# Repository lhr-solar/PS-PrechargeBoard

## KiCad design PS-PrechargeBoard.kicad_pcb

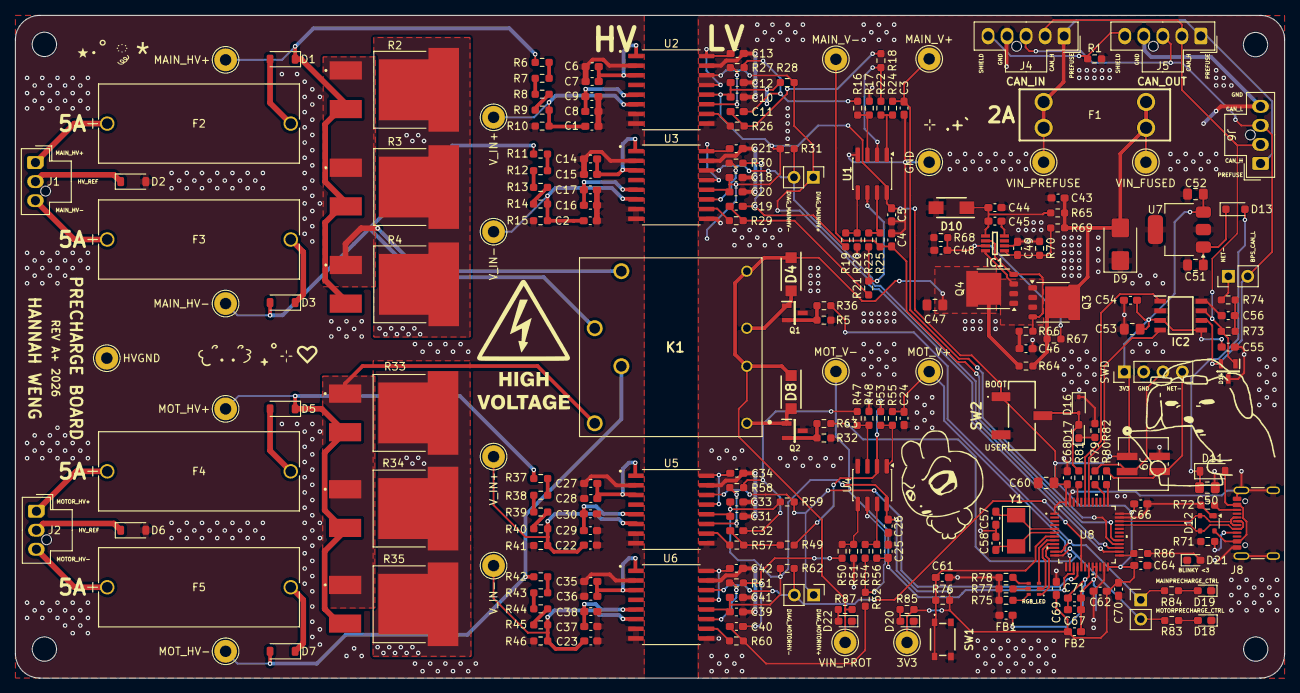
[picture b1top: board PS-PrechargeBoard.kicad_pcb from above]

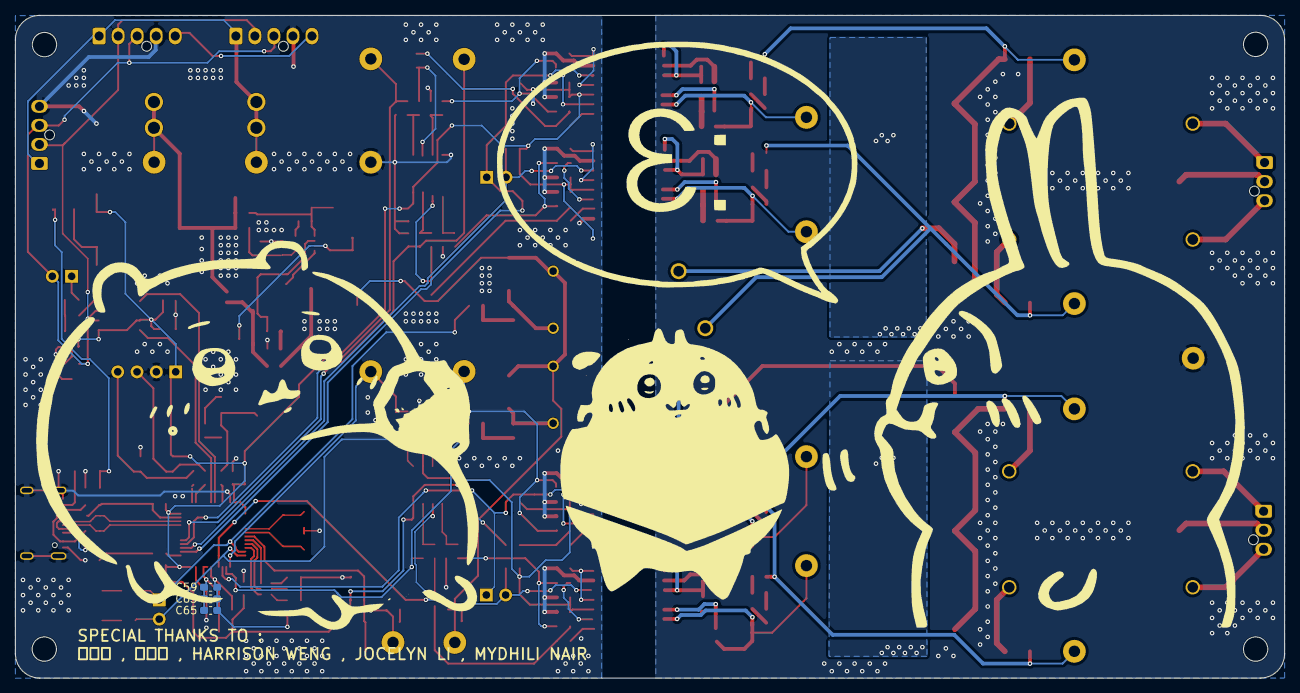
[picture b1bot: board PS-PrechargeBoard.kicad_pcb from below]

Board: 2 copper layers, 166.9 x 87.1 mm, 239 parts (3 on the bottom side), 139 nets.

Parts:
C1, C2, C5, C10, C18, C22, C23, C26, C31, C39, C44, C65, C67: 1u; C_0603_1608Metric_Pad1.08x0.95mm_HandSolder
C3, C4, C11, C19, C24, C25, C32, C40, C46: 10n; C_0603_1608Metric_Pad1.08x0.95mm_HandSolder
C6, C9, C12, C14, C17, C20, C27, C30, C33, C35, C38, C41: 1n; C_0603_1608Metric_Pad1.08x0.95mm_HandSolder
C7, C8, C13, C15, C16, C21, C28, C29, C34, C36, C37, C42, C71: 100n; C_0603_1608Metric_Pad1.08x0.95mm_HandSolder
C43, C48, C49, C54, C55, C56, C59, C61, C62, C63, C64, C66, C68, C69, C70: 0.1u; C_0603_1608Metric_Pad1.08x0.95mm_HandSolder
C45: 220n; C_0603_1608Metric_Pad1.08x0.95mm_HandSolder
C47, C50, C51, C52, C53, C60: 10u; C_0805_2012Metric_Pad1.18x1.45mm_HandSolder
C57, C58: 26p; C_0603_1608Metric_Pad1.08x0.95mm_HandSolder
D1, D2, D3, D5, D6, D7: RSX068MP2STR; D_SOD-123
D4, D8: VSSAF510HM3/H; SODFL5226X100N
D9: SMBJ15CA; D_SMB
D10: SMAF4758A; SODFL5026X125N
D11: D_Schottky; D_SOD-123
D12: SP0503BAHT; SOT-143
D13: SBA130CH-AU_R1_000A1; D_SOD-323_HandSoldering
D14: CDSOT23-T24CAN
D15: RGB_LED
D16: TVS; D_SOD-323
D17, D18, D19, D20, D21, D22: LED; LED_0603_1608Metric_Pad1.05x0.95mm_HandSolder
F1: 2A; Fuse-3557-2
F2, F3, F4, F5: 5A; HV-Fuse
FB1, FB2: FerriteBead; C_0603_1608Metric_Pad1.08x0.95mm_HandSolder
H1, H2, H3, H4: MountingHole; MountingHole_3.2mm_M3
IC1: LM74502DDFR
IC2: TCAN3413DR
J1: HV_Main; Molex_Nano-Fit_105309-xx03_1x03_P2.50mm_Vertical
J2: HV_Motor; Molex_Nano-Fit_105309-xx03_1x03_P2.50mm_Vertical
J3: MOTOR_DIAG; PinHeader_1x02_P2.54mm_Vertical
J4: CAN_IN; Molex_Nano-Fit_105309-xx05_1x05_P2.50mm_Vertical
J5: CAN_OUT; Molex_Nano-Fit_105309-xx05_1x05_P2.50mm_Vertical
J6: DEBUG_NANO; Molex_Nano-Fit_105309-xx04_1x04_P2.50mm_Vertical
J7: PRECHARGE_CTRL; PinHeader_1x02_P2.54mm_Vertical
J8: USB_C_Receptacle_USB2.0_16P; USB_C_Receptacle_GCT_USB4105-xx-A_16P_TopMnt_Horizontal
J9: SWD_Header; SWD_Conn
J10: SWD; PinHeader_1x04_P2.54mm_Vertical
J11: MAIN_DIAG; PinHeader_1x02_P2.54mm_Vertical
JP1: TRM; PinHeader_1x02_P2.54mm_Vertical
K1: FTR-J2AK012W; FTRJ2AK012W
Q1, Q2: NMOS; SOT95P237X112-3N
Q3, Q4: PSMN012-100YS; LFPAK56
R1, R64: 0; R_0603_1608Metric_Pad0.98x0.95mm_HandSolder
R2, R3, R4, R33, R34, R35: 50; RES_PWR263S-35-3300F
R5, R10, R15, R16, R17, R18, R19, R20, R21, R22, R23, R32, R41, R46, R47, R48, R49, R50, R51, R52, R53, R54, R65, R76, R81: 10k; R_0603_1608Metric_Pad0.98x0.95mm_HandSolder
R6, R7, R8, R9, R11, R12, R13, R14, R37, R38, R39, R40, R42, R43, R44, R45: 180k; R_0603_1608Metric_Pad0.98x0.95mm_HandSolder
R24, R25, R26, R27, R29, R30, R55, R56, R57, R58, R60, R61: 10; R_0603_1608Metric_Pad0.98x0.95mm_HandSolder
R28, R31, R59, R62: 47k; R_0603_1608Metric_Pad0.98x0.95mm_HandSolder
R36, R63: 100; R_0603_1608Metric_Pad0.98x0.95mm_HandSolder
R66: 33; R_0603_1608Metric_Pad0.98x0.95mm_HandSolder
R67, R69: 100k; R_0603_1608Metric_Pad0.98x0.95mm_HandSolder
R68: 7.32k; R_0603_1608Metric_Pad0.98x0.95mm_HandSolder
R70: 15.8k; R_0603_1608Metric_Pad0.98x0.95mm_HandSolder
R71, R72: 5.1k; R_0603_1608Metric_Pad0.98x0.95mm_HandSolder
R73, R74: 60; R_0603_1608Metric_Pad0.98x0.95mm_HandSolder
R75, R77, R78, R82, R83, R84, R85, R86: 1k; R_0603_1608Metric_Pad0.98x0.95mm_HandSolder
R79, R80: 22; R_0603_1608Metric_Pad0.98x0.95mm_HandSolder
R87: 4.7k; R_0603_1608Metric_Pad0.98x0.95mm_HandSolder
SW1: Reset; TL3365AF180QG
SW2: SW_SPDT; BootSW
TP1: MOT_HV+; TestPoint_THTPad_D3.0mm_Drill1.5mm
TP2: MAIN_HV+; TestPoint_THTPad_D3.0mm_Drill1.5mm
TP3: HVGND; TestPoint_THTPad_D3.0mm_Drill1.5mm
TP4: MAIN_HV-; TestPoint_THTPad_D3.0mm_Drill1.5mm
TP5: MOT_HV-; TestPoint_THTPad_D3.0mm_Drill1.5mm
TP6: 3V3; TestPoint_THTPad_D3.0mm_Drill1.5mm
TP7: VIN_PROT; TestPoint_THTPad_D3.0mm_Drill1.5mm
TP8: VIN_PREFUSE; TestPoint_THTPad_D3.0mm_Drill1.5mm
TP9: MAIN_V+; TestPoint_THTPad_D3.0mm_Drill1.5mm
TP10: MAIN_V-; TestPoint_THTPad_D3.0mm_Drill1.5mm
TP11: GND; TestPoint_THTPad_D3.0mm_Drill1.5mm
TP12: VIN_FUSED; TestPoint_THTPad_D3.0mm_Drill1.5mm
TP13: MOT_V+; TestPoint_THTPad_D3.0mm_Drill1.5mm
TP14: MOT_V-; TestPoint_THTPad_D3.0mm_Drill1.5mm
TP15, TP19: V_IN+; TestPoint_THTPad_D3.0mm_Drill1.5mm
TP16, TP20: V_IN-; TestPoint_THTPad_D3.0mm_Drill1.5mm
U1, U4: TLV9002QDRQ1; SOIC-8_3.9x4.9mm_P1.27mm
U2, U3, U5, U6: SOIC127P1030X265-16N
U7: MCP1826S; SOT-223-3_TabPin2
U8: STM32G473CETx; 48PinMCU
Y1: Crystal; Crystal_SMD_Abracon_ABM3-2Pin_5.0x3.2mm

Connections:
3V3: C5.1, C10.1, C12.1, C18.1, C20.1, C26.1, C31.1, C33.1, C39.1, C41.1, C52.2, C53.1, C54.1, C55.1, C60.1, C62.1, C64.1, C66.1, C68.1, C69.1, C70.1, FB2.1, IC2.3 (VCC), IC2.5 (SHDNV_IO), J9.1, J10.1, R28.1, R31.1, R59.1, R62.1, R76.2, R85.1, SW2.1 (A), TP6.1 (1_1), U1.8 (V+), U2.12 (VDD), U3.12 (VDD), U4.8 (V+), U5.12 (VDD), U6.12 (VDD), U7.3 (VO), U8.1 (VBAT), U8.24 (VDD), U8.36 (VDD), U8.48 (VDD)
/48PinMCU/BOOT0: R81.1, U8.45 (PB8-BOOT0)
/48PinMCU/GNDA: C59.2, C63.2, C65.2, C67.2, C71.2, FB1.1, U8.19 (VSSA)
/48PinMCU/NRST: C61.1, R76.1, SW1.1, U8.7 (PG10-NRST)
/48PinMCU/PA0: D15.5, U8.8 (PA0-GPIO_BLUE)
/48PinMCU/PA1: D15.3, U8.9 (PA1_GPIO_RED)
/48PinMCU/PA2: D15.1, U8.10 (PA2-GPIO_GREEN)
/48PinMCU/SWCLK: R79.1, U8.38 (PA14)
/48PinMCU/SWDIO: R80.1, U8.37 (PA13)
/48PinMCU/VDDA: C59.1, C63.1, C65.1, C67.1, C71.1, FB2.2, U8.20 (VREF+), U8.21 (VDDA)
/BLINKY: R86.1, U8.25 (PB11)
/BPS_CAN_H: D14.1 (CAN_H), IC2.7 (CANH), J4.2 (CAN_H), J5.2 (CAN_H), J6.2 (CAN_H), R73.1
/BPS_CAN_L: D14.2 (CAN_L), IC2.6 (CANL), J4.3 (CAN_L), J5.3 (CAN_L), J6.3 (CAN_L), JP1.2 (B)
/CAN_RX: IC2.4 (RXD), U8.42 (PB5)
/CAN_TX: IC2.1 (TXD), U8.43 (PB6)
/DIAG_MAINHV+: J11.1, R28.2, U2.14 (DIAG), U8.26 (PB12)
/DIAG_MAINHV-: J11.2, R31.2, U3.14 (DIAG), U8.27 (PB13)
/DIAG_MOTORHV+: J3.1, R59.2, U5.14 (DIAG), U8.16 (PB0)
/DIAG_MOTORHV-: J3.2, R62.2, U6.14 (DIAG), U8.17 (PB1)
/LV Power/PowerProtection/EN/UVLO: C49.1, IC1.1 (EN/UVLO), R69.2, R70.2
/LV Power/PowerProtection/OV: C48.1, IC1.7 (OV), R67.2, R68.1
/LV Power/PowerProtection/gate: IC1.6 (GATE), Q3.4, Q4.4, R66.2
/LV Power/PowerProtection/source: IC1.8 (SRC), Q3.1, Q3.2, Q3.3, Q4.1, Q4.2, Q4.3
/LV Power/USB-C_Connector/CC1: J8.A5 (CC1), R71.2
/LV Power/USB-C_Connector/CC2: J8.B5 (CC2), R72.2
/LV Power/USB-C_Connector/VBUS_IN: D11.2 (A), D12.4 (K), J8.A4 (VBUS), J8.A9 (VBUS), J8.B4 (VBUS), J8.B9 (VBUS)
/LV Power/USB_5V: C50.2, D11.1 (K), D13.2 (A)
/MAINPRECHARGE_CTRL: J7.1, R36.1, R84.1, U8.11 (PA3)
/MAIN_RES_HV-: K1.8 (COM_2), R2.1, R3.1, R4.1
/MAIN_V+: C3.1, R24.2, TP9.1 (1_1), U8.28 (PB14)
/MAIN_V-: C4.1, R25.2, TP10.1 (1_1), U8.29 (PB15)
/MOTPRECHARGE_CTRL: J7.2, R63.1, R83.1, U8.12 (PA4)
/MOT_RES_HV-: K1.5 (NO_1), R33.1, R34.1, R35.1
/MOT_V+: C24.1, R55.2, TP13.1 (1_1), U8.14 (PA6)
/MOT_V-: C25.1, R56.2, TP14.1 (1_1), U8.15 (PA7)
/Main_Fuse/HV_PREFUSE+: F2.1, J1.1
/Main_Fuse/HV_PREFUSE-: F3.1, J1.3
/Main_Fuse/HV_REF: D2.1 (K), J1.2
/Main_Fuse/RESISTOR: R2.3, R3.3, R4.3
/Main_VoltageSensor/OUTN_HV+: C11.1, R18.1, R26.2
/Main_VoltageSensor/OUTN_HV-: C19.1, R21.1, R29.2
/Main_VoltageSensor/OUTP_HV+: C11.2, R16.1, R27.2
/Main_VoltageSensor/OUTP_HV-: C19.2, R19.1, R30.2
/Main_VoltageSensor/V_IN+: C1.1, R9.2, R10.1, TP15.1 (1_1), U2.6 (IN)
/Main_VoltageSensor/V_IN-: C2.1, R14.2, R15.1, TP16.1 (1_1), U3.6 (IN)
/Main_VoltageSensor/VoltageSensor_HV+/3V3_DCDC: C13.2, U2.13 (LDO_OUT), U2.16 (DCDC_IN)
/Main_VoltageSensor/VoltageSensor_HV+/HLDO_OUT: C8.2, C9.2, U2.5 (HLDO_OUT)
/Main_VoltageSensor/VoltageSensor_HV+/HV_DCDC: C6.1, C7.2, U2.1 (DCDC_OUT), U2.3 (HLDO_IN)
/Main_VoltageSensor/VoltageSensor_HV+/OUTN: R26.1, U2.10 (OUTN)
/Main_VoltageSensor/VoltageSensor_HV+/OUTP: R27.1, U2.11 (OUTP)
/Main_VoltageSensor/VoltageSensor_HV-/3V3_DCDC: C21.2, U3.13 (LDO_OUT), U3.16 (DCDC_IN)
/Main_VoltageSensor/VoltageSensor_HV-/HLDO_OUT: C16.2, C17.2, U3.5 (HLDO_OUT)
/Main_VoltageSensor/VoltageSensor_HV-/HV_DCDC: C14.1, C15.2, U3.1 (DCDC_OUT), U3.3 (HLDO_IN)
/Main_VoltageSensor/VoltageSensor_HV-/OUTN: R29.1, U3.10 (OUTN)
/Main_VoltageSensor/VoltageSensor_HV-/OUTP: R30.1, U3.11 (OUTP)
/Motor_Fuse/HV_PREFUSE+: F4.1, J2.1
/Motor_Fuse/HV_PREFUSE-: F5.1, J2.3
/Motor_Fuse/HV_REF: D6.1 (K), J2.2
/Motor_Fuse/RESISTOR: R33.3, R34.3, R35.3
/Motor_VoltageSensor/OUTN_HV+: C32.1, R49.1, R57.2
/Motor_VoltageSensor/OUTN_HV-: C40.1, R52.1, R60.2
/Motor_VoltageSensor/OUTP_HV+: C32.2, R47.1, R58.2
/Motor_VoltageSensor/OUTP_HV-: C40.2, R50.1, R61.2
/Motor_VoltageSensor/V_IN+: C22.1, R40.2, R41.1, TP19.1 (1_1), U5.6 (IN)
/Motor_VoltageSensor/V_IN-: C23.1, R45.2, R46.1, TP20.1 (1_1), U6.6 (IN)
/Motor_VoltageSensor/VoltageSensor_HV+/3V3_DCDC: C34.2, U5.13 (LDO_OUT), U5.16 (DCDC_IN)
/Motor_VoltageSensor/VoltageSensor_HV+/HLDO_OUT: C29.2, C30.2, U5.5 (HLDO_OUT)
/Motor_VoltageSensor/VoltageSensor_HV+/HV_DCDC: C27.1, C28.2, U5.1 (DCDC_OUT), U5.3 (HLDO_IN)
/Motor_VoltageSensor/VoltageSensor_HV+/OUTN: R57.1, U5.10 (OUTN)
/Motor_VoltageSensor/VoltageSensor_HV+/OUTP: R58.1, U5.11 (OUTP)
/Motor_VoltageSensor/VoltageSensor_HV-/3V3_DCDC: C42.2, U6.13 (LDO_OUT), U6.16 (DCDC_IN)
/Motor_VoltageSensor/VoltageSensor_HV-/HLDO_OUT: C37.2, C38.2, U6.5 (HLDO_OUT)
/Motor_VoltageSensor/VoltageSensor_HV-/HV_DCDC: C35.1, C36.2, U6.1 (DCDC_OUT), U6.3 (HLDO_IN)
/Motor_VoltageSensor/VoltageSensor_HV-/OUTN: R60.1, U6.10 (OUTN)
/Motor_VoltageSensor/VoltageSensor_HV-/OUTP: R61.1, U6.11 (OUTP)
/Precharge_Relay/MAIN_DRAIN: D4.2 (A), K1.3 (COIL2_1), Q1.1 (D)
/Precharge_Relay/MOT_DRAIN: D8.2 (A), K1.1 (COIL1_1), Q2.1 (D)
/SHIELD: J4.5 (SHIELD), J5.5 (SHIELD), R1.1
/USB_D+: D12.2 (K), J8.A6 (D+), J8.B6 (D+), U8.34 (PA12)
/USB_D-: D12.3 (K), J8.A7 (D-), J8.B7 (D-), U8.33 (PA11)
/VIN_FUSED: C43.1, D9.2 (A2), F1.1, Q3.5, R64.1, R65.2, R67.1, R69.1, TP12.1 (1_1)
/VIN_PREFUSE: F1.2, J4.1 (12V), J5.1 (12V), J6.1 (12V), TP8.1 (1_1)
GND: C3.2, C4.2, C5.2, C10.2, C12.2, C13.1, C18.2, C20.2, C21.1, C24.2, C25.2, C26.2, C31.2, C33.2, C34.1, C39.2, C41.2, C42.1, C43.2, C44.1, C46.2, C47.2, C48.2, C49.2, C50.1, C51.1, C52.1, C53.2, C54.2, C55.2, C56.1, C57.1, C58.2, C60.2, C61.2, C62.2, C64.2, C66.2, C68.2, C69.2, C70.2, D9.1 (A1), D10.2 (A), D12.1 (A), D14.3 (GND), D16.1 (A1), D18.1 (K), D19.1 (K), D20.1 (K), D21.1 (K), D22.1 (K), FB1.2, IC1.2 (GND), IC2.2 (GND), IC2.8 (STB), J4.4 (GND), J5.4 (GND), J6.4 (GND), J8.A1 (GND), J8.A12 (GND), J8.B1 (GND), J8.B12 (GND), J8.S1 (SHIELD), J8.S2 (Shield), J8.S3 (Shield), J8.S4 (Shield), J9.2, J10.2, Q1.3 (S), Q2.3 (S), R1.2, R5.1, R17.2, R20.2, R32.1, R48.2, R51.2, R68.2, R70.1, R71.1, R72.1, R75.2, R77.2, R78.2, R82.2, SW1.2, SW2.3 (C), TP11.1 (1_1), U1.4 (V-), U2.9 (GND), U2.15 (DCDC_GND), U3.9 (GND), U3.15 (DCDC_GND), U4.4 (V-), U5.9 (GND), U5.15 (DCDC_GND), U6.9 (GND), U6.15 (DCDC_GND), U7.2 (GND), U8.23 (VSS), U8.35 (VSS), U8.47 (VSS)
HVGND: C1.2, C2.2, C6.2, C7.1, C8.1, C9.1, C14.2, C15.1, C16.1, C17.1, C22.2, C23.2, C27.2, C28.1, C29.1, C30.1, C35.2, C36.1, C37.1, C38.1, D2.2 (A), D6.2 (A), R10.2, R15.2, R41.2, R46.2, TP3.1 (1_1), U2.2 (DCDC_HGND), U2.7 (HGND), U2.8 (HGND), U3.2 (DCDC_HGND), U3.7 (HGND), U3.8 (HGND), U5.2 (DCDC_HGND), U5.7 (HGND), U5.8 (HGND), U6.2 (DCDC_HGND), U6.7 (HGND), U6.8 (HGND)
MAIN_HV+: D1.1 (K), R2.2, R3.2, R4.2, R6.1, TP2.1 (1_1)
MAIN_HV-: D3.2 (A), K1.7 (NO_2), R11.1, TP4.1 (1_1)
MOT_HV+: D5.1 (K), R33.2, R34.2, R35.2, R37.1, TP1.1 (1_1)
MOT_HV-: D7.2 (A), K1.6 (COM_1), R42.1, TP5.1 (1_1)
unnamed: C46.1, R66.1
unnamed: C56.2, R73.2, R74.1
unnamed: D1.2 (A), F2.2
unnamed: D3.1 (K), F3.2
unnamed: D5.2 (A), F4.2
unnamed: D7.1 (K), F5.2
unnamed: C44.2, C45.1, D10.1 (K), IC1.5 (VS), R65.1
unnamed: C51.2, D13.1 (K), U7.1 (VI)
unnamed: D15.2, R75.1
unnamed: D15.4, R77.1
unnamed: D15.6, R78.1
unnamed: D16.2 (A2), D17.2 (A), R81.2, SW2.2 (B)
unnamed: D17.1 (K), R82.1
unnamed: D18.2 (A), R83.2
unnamed: D19.2 (A), R84.2
unnamed: D20.2 (A), R85.2
unnamed: D21.2 (A), R86.2
unnamed: D22.2 (A), R87.2
unnamed: C45.2, IC1.4 (VCAP)
unnamed: J9.3, J10.3, R79.2
unnamed: J9.4, J10.4, R80.2
unnamed: JP1.1 (A), R74.2
unnamed: Q1.2 (G), R5.2, R36.2
unnamed: Q2.2 (G), R32.2, R63.2
unnamed: R6.2, R7.1
unnamed: R7.2, R8.1
unnamed: R8.2, R9.1
unnamed: R11.2, R12.1
unnamed: R12.2, R13.1
unnamed: R13.2, R14.1
unnamed: R22.2, R24.1, U1.1
unnamed: R23.2, R25.1, U1.7
unnamed: R37.2, R38.1
unnamed: R38.2, R39.1
unnamed: R39.2, R40.1
unnamed: R42.2, R43.1
unnamed: R43.2, R44.1
unnamed: R44.2, R45.1
unnamed: R53.2, R55.1, U4.1
unnamed: R54.2, R56.1, U4.7
unnamed: R16.2, R17.1, U1.3 (+)
unnamed: R18.2, R22.1, U1.2 (-)
unnamed: R19.2, R20.1, U1.5 (+)
unnamed: R21.2, R23.1, U1.6 (-)
unnamed: R47.2, R48.1, U4.3 (+)
unnamed: R49.2, R53.1, U4.2 (-)
unnamed: R50.2, R51.1, U4.5 (+)
unnamed: R52.2, R54.1, U4.6 (-)
unnamed: C57.2, U8.5 (PF0-OSC_IN), Y1.1
unnamed: C58.1, U8.6 (PF1-OSC_OUT), Y1.2
VIN_PROT: C47.1, D4.1 (K), D8.1 (K), K1.2 (COIL1_2), K1.4 (COIL2_2), Q4.5, R64.2, R87.1, TP7.1 (1_1)

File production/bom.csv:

Designator,Footprint,Quantity,Value,LCSC Part #
"C1, C10, C18, C2, C22, C23, C26, C31, C39, C44, C5, C65, C67",0603,13,1u,C15849
"C11, C19, C24, C25, C3, C32, C4, C40, C46",0603,9,10n,C100042
"C12, C14, C17, C20, C27, C30, C33, C35, C38, C41, C6, C9",0603,12,1n,
"C13, C15, C16, C21, C28, C29, C34, C36, C37, C42, C7, C71, C8",0603,13,100n,C15849
"C43, C48, C49, C54, C55, C56, C59, C61, C62, C63, C64, C66, C68, C69, C70",0603,15,0.1u,C14663
C45,0603,1,220n,C107083
"C47, C50, C51, C52, C53, C60",0805,6,10u,C440198
"C57, C58",0603,2,26p,C92670
"D1, D2, D3, D5, D6, D7",D_SOD-123,6,RSX068MP2STR,
D10,SODFL5026X125N,1,SMAF4758A,C183490
D11,D_SOD-123,1,D_Schottky,C82544
D12,SOT-143,1,SP0503BAHT,C7074
D13,D_SOD-323_HandSoldering,1,SBA130CH-AU_R1_000A1,C191023
D14,CDSOT23-T24CAN,1,CDSOT23-T24CAN,C2959841
D15,RGB_LED,1,RGB_LED,C264519
D16,D_SOD-323,1,TVS,C725495
"D17, D18, D19, D20, D21, D22",0603,6,LED,C125103
"D4, D8",SODFL5226X100N,2,VSSAF510HM3/H,
D9,D_SMB,1,SMBJ15CA,C669039
F1,Fuse-3557-2,1,2A,C3205238
"F2, F3, F4, F5",HV-Fuse,4,5A,
"FB1, FB2",0603,2,FerriteBead,C354394
IC1,LM74502DDFR,1,LM74502DDFR,C3236215
IC2,TCAN3413DR,1,TCAN3413DR,C22433320
J1,Molex_Nano-Fit_105309-xx03_1x03_P2.50mm_Vertical,1,HV_Main,
J2,Molex_Nano-Fit_105309-xx03_1x03_P2.50mm_Vertical,1,HV_Motor,
J4,Molex_Nano-Fit_105309-xx05_1x05_P2.50mm_Vertical,1,CAN_IN,
J5,Molex_Nano-Fit_105309-xx05_1x05_P2.50mm_Vertical,1,CAN_OUT,
J6,Molex_Nano-Fit_105309-xx04_1x04_P2.50mm_Vertical,1,DEBUG_NANO,
J7,PinHeader_1x02_P2.54mm_Vertical,1,PRECHARGE_CTRL,
J8,USB_C_Receptacle_GCT_USB4105-xx-A_16P_TopMnt_Horizontal,1,USB_C_Receptacle_USB2.0_16P,C3020560
J9,SWD_Conn,1,SWD_Header,C17492485
K1,FTRJ2AK012W,1,FTR-J2AK012W,
"Q1, Q2",SOT95P237X112-3N,2,NMOS,
"Q3, Q4",LFPAK56,2,PSMN012-100YS,C20443035
"R1, R64",0603,2,0,
"R10, R15, R16, R17, R18, R19, R20, R21, R22, R23, R32, R41, R46, R47, R48, R49, R5, R50, R51, R52, R53, R54, R65, R76, R81",0603,25,10k,C20443035
"R11, R12, R13, R14, R37, R38, R39, R40, R42, R43, R44, R45, R6, R7, R8, R9",0603,16,180k,
"R2, R3, R33, R34, R35, R4",RES_PWR263S-35-3300F,6,50,
"R24, R25, R26, R27, R29, R30, R55, R56, R57, R58, R60, R61",0603,12,10,
"R28, R31, R59, R62",0603,4,47k,
"R36, R63",0603,2,100,
R66,0603,1,33,C2074308
"R67, R69",0603,2,100k,C25803
R68,0603,1,7.32k,C862286
R70,0603,1,15.8k,C843918
"R71, R72",0603,2,5.1k,C23186
"R73, R74",0603,2,60,C166918
"R75, R77, R78, R82, R83, R84, R85, R86",0603,8,1k,C21190
"R79, R80",0603,2,22,C2930077
R87,0603,1,4.7k,C21190
SW1,TL3365AF180QG,1,Reset,C2886926
SW2,BootSW,1,SW_SPDT,-
"U1, U4",SOIC-8_3.9x4.9mm_P1.27mm,2,TLV9002QDRQ1,
"U2, U3, U5, U6",SOIC127P1030X265-16N,4,~,
U7,SOT-223-3_TabPin2,1,MCP1826S,C126055
U8,48PinMCU,1,STM32G473CETx,C730113
Y1,Crystal_SMD_Abracon_ABM3-2Pin_5.0x3.2mm,1,Crystal,C144380

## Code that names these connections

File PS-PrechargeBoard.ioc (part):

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Mcu.Name=STM32G473C(B-C-E)Tx
Mcu.Package=LQFP48
Mcu.UserName=STM32G473CETx
PA11.Mode=Device
PA11.Signal=USB_DM
PA12.Mode=Device
PA12.Signal=USB_DP
PA3.Signal=GPIO_Output
PA4.Signal=GPIO_Output
PA6.Mode=IN3-Differential
PA6.Signal=ADC2_IN3
PA7.Mode=IN3-Differential
PA7.Signal=ADC2_IN4
PB0.Signal=GPIO_Input
PB1.Signal=GPIO_Input
PB12.Signal=GPIO_Input
PB13.Signal=GPIO_Input
PB14.Mode=IN4-Differential
PB14.Signal=ADC4_IN4
PB15.Mode=IN4-Differential
PB15.Signal=ADC4_IN5
PB5.Mode=FDCAN_Activate
PB5.Signal=FDCAN2_RX
PB6.Mode=FDCAN_Activate
PB6.Signal=FDCAN2_TX
PF0-OSC_IN.Mode=HSE-External-Oscillator
PF0-OSC_IN.Signal=RCC_OSC_IN
PF1-OSC_OUT.Mode=HSE-External-Oscillator
PF1-OSC_OUT.Signal=RCC_OSC_OUT
RCC.HSE_VALUE=8000000
RCC.SYSCLKFreq_VALUE=16000000
board=custom
